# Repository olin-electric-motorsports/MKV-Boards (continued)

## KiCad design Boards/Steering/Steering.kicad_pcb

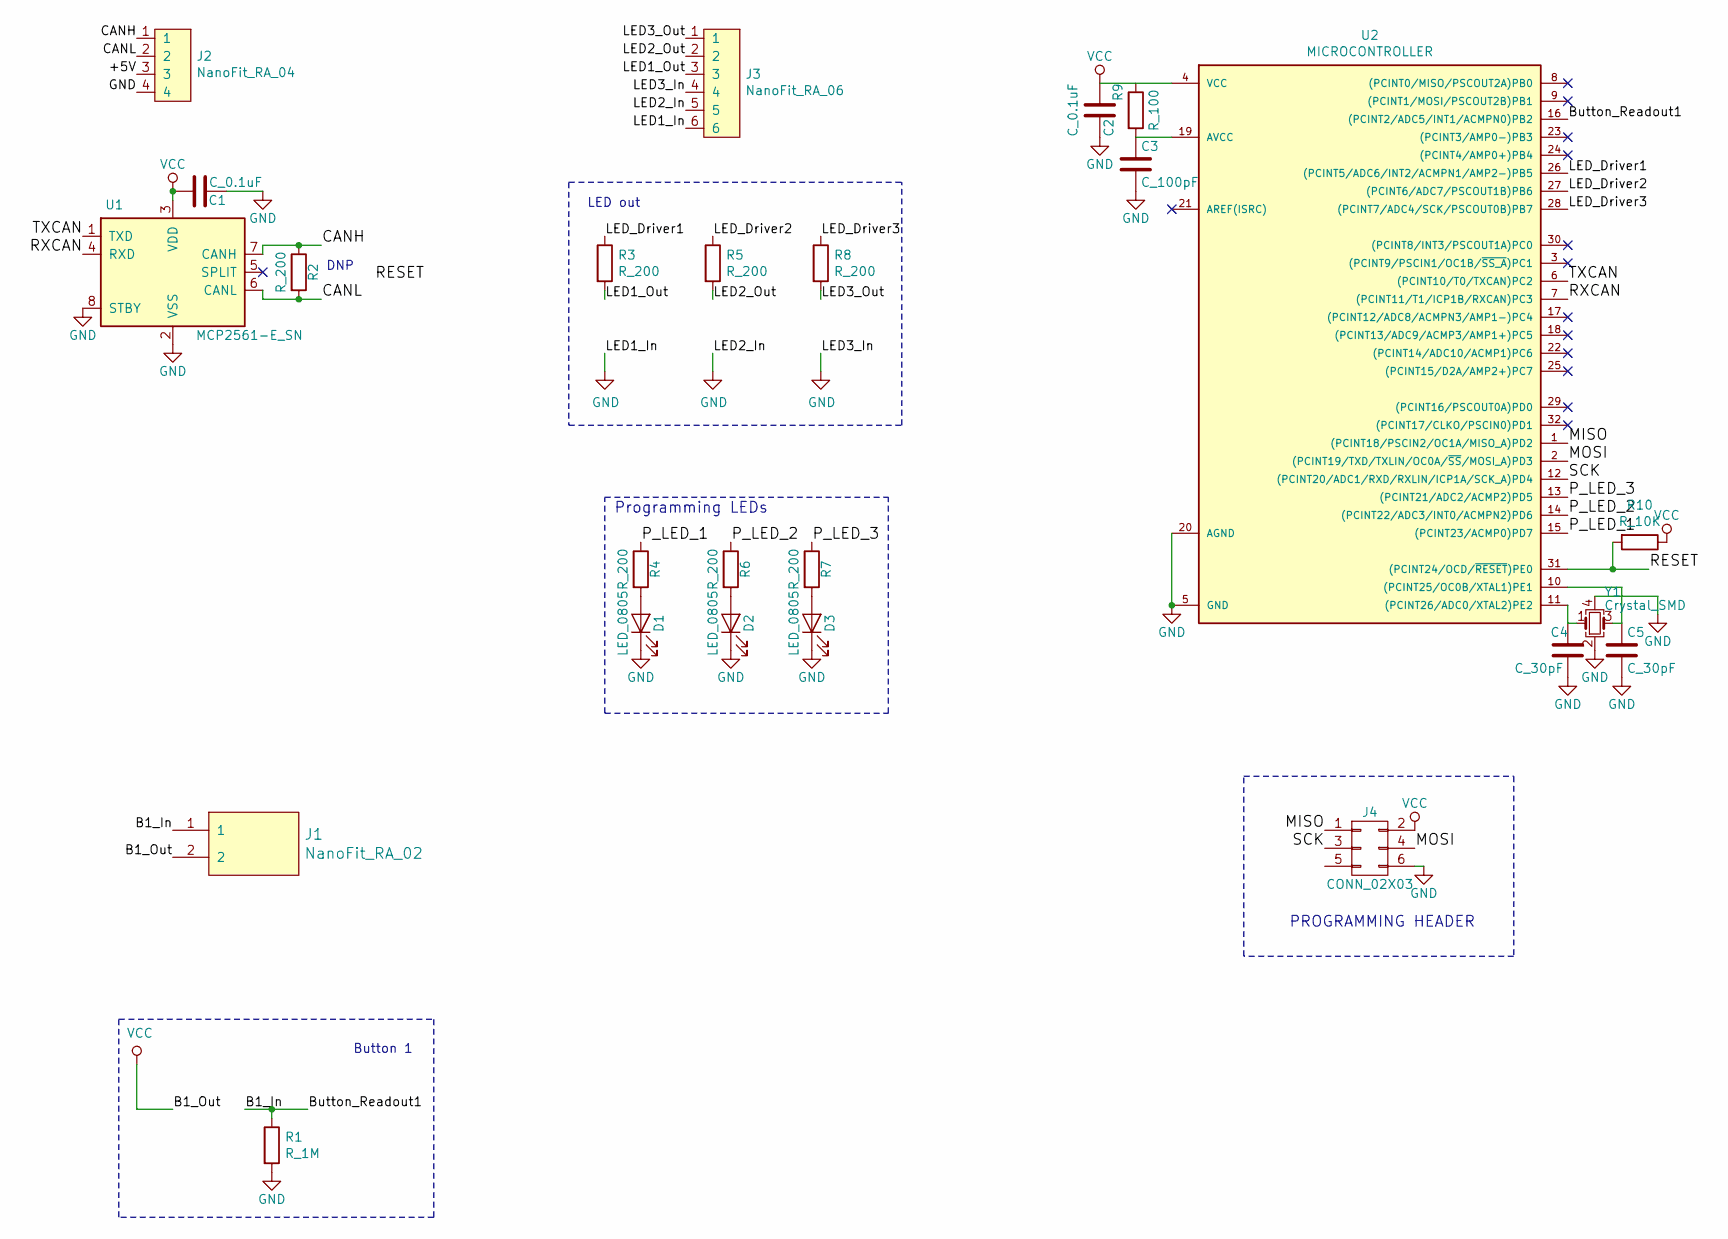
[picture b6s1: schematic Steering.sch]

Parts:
C1, C2: C_0.1uF; C_0805_OEM; MPN 478-3352-1-ND
C3: C_100pF; C_0805_OEM; MPN 399-1122-1-ND
C4, C5: C_30pF; C_0805_OEM; MPN 1276-1130-1-ND
D1, D2, D3: LED_0805; LED_0805_OEM; MPN 475-1410-1-ND
J1: NanoFit_RA_02; NanoFit_Molex_1x02x2.50mm_Angled_OEM; MPN WM14972-ND
J2: NanoFit_RA_04; NanoFit_RA_4
J3: NanoFit_RA_06; NanoFit_RA_6
J4: CONN_02X03; Pin_Header_Straight_2x03; MPN 609-3234-ND
R1: R_1M; R_0805_OEM; MPN RMCF0805JT1M00CT-ND
R2, R3, R4, R5, R6, R7, R8: R_200; R_0805_OEM; MPN RMCF0805JT200RCT-ND
R9: R_100; R_0805_OEM; MPN RNCP0805FTD100RCT-ND
R10: R_10K; R_0805_OEM; MPN CRS0805-FX-1002ELFCT-ND
U1: MCP2561-E_SN; SOIC-8_3.9x4.9mm_Pitch1.27mm_OEM; MPN MCP2561-E/SN-ND
U2: MICROCONTROLLER; TQFP-32_7x7mm_Pitch0.8mm; MPN ATMEGA16M1-AU-ND
Y1: Crystal_SMD; Crystal_SMD_FA238; MPN SER3686CT-ND

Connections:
/+5V: J2.3
/B1_In: J1.1, R1.1, U2.16 ((PCINT2/ADC5/INT1/ACMPN0)PB2)
/CANH: J2.1, R2.1, U1.7 (CANH)
/CANL: J2.2, R2.2, U1.6 (CANL)
/LED1_Out: J3.3, R3.2
/LED2_Out: J3.2, R5.2
/LED3_Out: J3.1, R8.2
/LED_Driver1: R3.1, U2.26 ((PCINT5/ADC6/INT2/ACMPN1/AMP2-)PB5)
/LED_Driver2: R5.1, U2.27 ((PCINT6/ADC7/PSCOUT1B)PB6)
/LED_Driver3: R8.1, U2.28 ((PCINT7/ADC4/SCK/PSCOUT0B)PB7)
/MISO: J4.1, U2.1 ((PCINT18/PSCIN2/OC1A/MISO_A)PD2)
/MOSI: J4.4, U2.2 ((PCINT19/TXD/TXLIN/OC0A/~SS~/MOSI_A)PD3)
/P_LED_1: R4.1, U2.15 ((PCINT23/ACMP0)PD7)
/P_LED_2: R6.1, U2.14 ((PCINT22/ADC3/INT0/ACMPN2)PD6)
/P_LED_3: R7.1, U2.13 ((PCINT21/ADC2/ACMP2)PD5)
/RESET: R10.2, U2.31 ((PCINT24/OCD/~RESET~)PE0)
/RXCAN: U1.4 (RXD), U2.7 ((PCINT11/T1/ICP1B/RXCAN)PC3)
/SCK: J4.3, U2.12 ((PCINT20/ADC1/RXD/RXLIN/ICP1A/SCK_A)PD4)
/TXCAN: U1.1 (TXD), U2.6 ((PCINT10/T0/TXCAN)PC2)
GND: C1.2, C2.2, C3.2, C4.2, C5.2, D1.1 (K), D2.1 (K), D3.1 (K), J2.4, J3.4, J3.5, J3.6, J4.6, R1.2, U1.2 (VSS), U1.8 (STBY), U2.5 (GND), U2.20 (AGND), Y1.2, Y1.4
unnamed: C3.1, R9.2, U2.19 (AVCC)
unnamed: C4.1, U2.11 ((PCINT26/ADC0/XTAL2)PE2), Y1.1
unnamed: C5.1, U2.10 ((PCINT25/OC0B/XTAL1)PE1), Y1.3
unnamed: D1.2 (A), R4.2
unnamed: D2.2 (A), R6.2
unnamed: D3.2 (A), R7.2
VCC: C1.1, C2.1, J1.2, J4.2, R10.1, U1.3 (VDD), U2.4 (VCC)

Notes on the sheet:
PROGRAMMING HEADER
Programming LEDs
LED out
DNP
Button 1

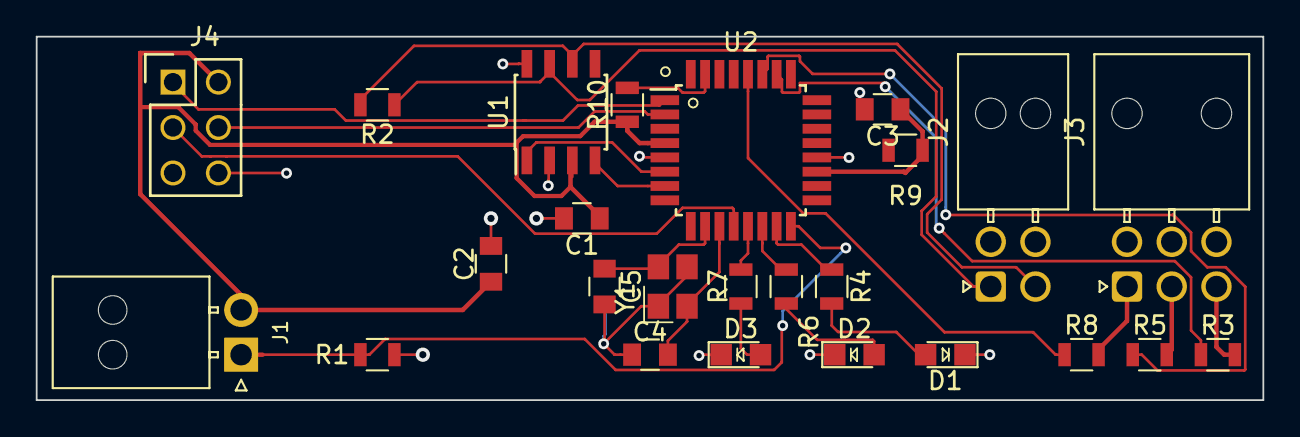
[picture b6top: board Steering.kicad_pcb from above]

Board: 2 copper layers, 68.6 x 20.3 mm, 25 parts (0 on the bottom side), 26 nets.
